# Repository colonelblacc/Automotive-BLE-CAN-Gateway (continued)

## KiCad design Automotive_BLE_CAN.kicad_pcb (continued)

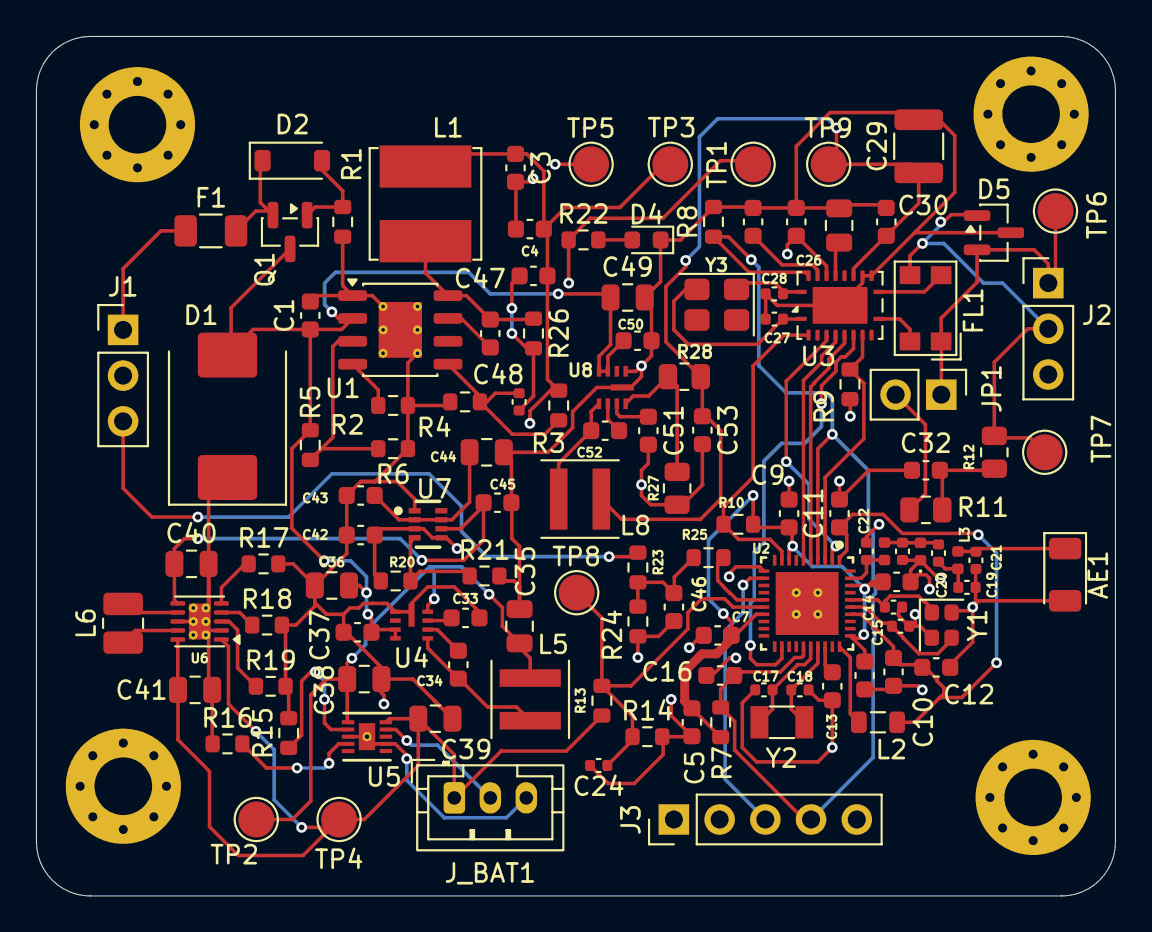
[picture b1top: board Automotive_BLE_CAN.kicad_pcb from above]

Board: 4 copper layers, 59.9 x 47.8 mm, 122 parts (0 on the bottom side), 70 nets.

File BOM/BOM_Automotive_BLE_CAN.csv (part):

Item,Designator,Qty,Value,Description,Package,Manufacturer,MPN,Ratings / Tolerance,Automotive Qual,Alternatives,Notes / Design Intent
1,AE1,1,Antenna_Chip,"2.45 GHz Ceramic Chip Antenna, Peak Gain 1.5 dBi, 50 Ohm",Johanson_2450AT18x100_2400-2500Mhz,Johanson Technology,2450AT18D0100E,,AEC-Q200 qualified option,"Pulse W3008, Taoglas GLA.01",Compact Bluetooth Low Energy omnidirectional antenna
2,C1,1,2.2uF,"2.2uF Ceramic Capacitor, Decoupling",C_0603_1608Metric,Murata / TDK / Taiyo Yuden,GCM188R71E2.2K,"16V / 25V, X7R, ±10%",AEC-Q200 Grade 1,,
3,C2,1,2.2nF,"2.2nF Ceramic Capacitor, Precision / High-Q",C_0603_1608Metric,Murata / TDK / Taiyo Yuden,GCM1885C1H2.2nFA01D,"50V, C0G/NP0 (RF) or X7R, ±5%",AEC-Q200 Grade 1,,
4,"C3, C53",2,22uF,"22uF Ceramic Capacitor, High Capacitance Low ESR",C_0603_1608Metric,Murata / TDK / Taiyo Yuden,GCM21BR71E226KA73L,"25V / 50V, X7R / X7S, ±10%",AEC-Q200 Grade 1,,
5,"C4, C30, C31, C34, C37, C46, C50, C52",8,100nF,"100nF Ceramic Capacitor, Precision / High-Q",C_0603_1608Metric,Murata / TDK / Taiyo Yuden,GCM1885C1H100nFA01D,"50V, C0G/NP0 (RF) or X7R, ±5%",AEC-Q200 Grade 1,,
6,"C5, C6, C7, C8, C9, C10, C11, C16",8,0.1uF,"0.1uF Ceramic Capacitor, Decoupling",C_0603_1608Metric,Murata / TDK / Taiyo Yuden,GCM188R71E0.1K,"16V / 25V, X7R, ±10%",AEC-Q200 Grade 1,,
7,C12,1,10uF,"10uF Ceramic Capacitor, High Capacitance Low ESR",C_0603_1608Metric,Murata / TDK / Taiyo Yuden,GCM21BR71E106KA73L,"25V / 50V, X7R / X7S, ±10%",AEC-Q200 Grade 1,,
8,"C13, C33, C42, C43, C45, C51",6,1uF,"1uF Ceramic Capacitor, Decoupling",C_0603_1608Metric,Murata / TDK / Taiyo Yuden,GCM188R71E1K,"16V / 25V, X7R, ±10%",AEC-Q200 Grade 1,,
9,"C14, C17",2,12pF,"12pF Ceramic Capacitor, Precision / High-Q",C_0402_1005Metric,Murata / TDK / Taiyo Yuden,GCM1555C1H12pFA01D,"50V, C0G/NP0 (RF) or X7R, ±5%",AEC-Q200 Grade 1,,
10,C15,1,10pF,"10pF Ceramic Capacitor, Precision / High-Q",C_0402_1005Metric,Murata / TDK / Taiyo Yuden,GCM1555C1H10pFA01D,"50V, C0G/NP0 (RF) or X7R, ±5%",AEC-Q200 Grade 1,,
11,"C18, C20",2,15pF,"15pF Ceramic Capacitor, Precision / High-Q",C_0402_1005Metric,Murata / TDK / Taiyo Yuden,GCM1555C1H15pFA01D,"50V, C0G/NP0 (RF) or X7R, ±5%",AEC-Q200 Grade 1,,
12,C19,1,1.2pF,"1.2pF Ceramic Capacitor, Precision / High-Q",C_0402_1005Metric,Murata / TDK / Taiyo Yuden,GCM1555C1H1.2pFA01D,"50V, C0G/NP0 (RF) or X7R, ±5%",AEC-Q200 Grade 1,,
13,C21,1,0.7pF,"0.7pF Ceramic Capacitor, Precision / High-Q",C_0402_1005Metric,Murata / TDK / Taiyo Yuden,GCM1555C1H0.7pFA01D,"50V, C0G/NP0 (RF) or X7R, ±5%",AEC-Q200 Grade 1,,
14,"C22, C23",2,1.5pF,"1.5pF Ceramic Capacitor, Precision / High-Q",C_0402_1005Metric,Murata / TDK / Taiyo Yuden,GCM1555C1H1.5pFA01D,"50V, C0G/NP0 (RF) or X7R, ±5%",AEC-Q200 Grade 1,,
15,C24,1,100nF,"100nF Ceramic Capacitor, Precision / High-Q",C_0402_1005Metric,Murata / TDK / Taiyo Yuden,GCM1555C1H100nFA01D,"50V, C0G/NP0 (RF) or X7R, ±5%",AEC-Q200 Grade 1,,
16,C25,1,330nF,"330nF Ceramic Capacitor, Precision / High-Q",C_0603_1608Metric,Murata / TDK / Taiyo Yuden,GCM1885C1H330nFA01D,"50V, C0G/NP0 (RF) or X7R, ±5%",AEC-Q200 Grade 1,,
17,"C27, C28",2,8.2pF,"8.2pF Ceramic Capacitor, Precision / High-Q",C_0402_1005Metric,Murata / TDK / Taiyo Yuden,GCM1555C1H8.2pFA01D,"50V, C0G/NP0 (RF) or X7R, ±5%",AEC-Q200 Grade 1,,
18,C29,1,10uF,"10uF Ceramic Capacitor, High Capacitance Low ESR",C_1210_3225Metric,Murata / TDK / Taiyo Yuden,GCM21BR71E106KA73L,"25V / 50V, X7R / X7S, ±10%",AEC-Q200 Grade 1,,
19,C32,1,4.7nF,"4.7nF Ceramic Capacitor, Precision / High-Q",C_0603_1608Metric,Murata / TDK / Taiyo Yuden,GCM1885C1H4.7nFA01D,"50V, C0G/NP0 (RF) or X7R, ±5%",AEC-Q200 Grade 1,,
20,"C35, C40",2,22uF,"22uF Ceramic Capacitor, High Capacitance Low ESR",C_0805_2012Metric,Murata / TDK / Taiyo Yuden,GCM21BR71E226KA73L,"25V / 50V, X7R / X7S, ±10%",AEC-Q200 Grade 1,,
21,"C36, C49",2,2.2uF,"2.2uF Ceramic Capacitor, Decoupling",C_0805_2012Metric,Murata / TDK / Taiyo Yuden,GCM188R71E2.2K,"16V / 25V, X7R, ±10%",AEC-Q200 Grade 1,,
22,"C38, C39",2,4.7uF,"4.7uF Ceramic Capacitor, Decoupling",C_0805_2012Metric,Murata / TDK / Taiyo Yuden,GCM188R71E4.7K,"16V / 25V, X7R, ±10%",AEC-Q200 Grade 1,,
23,"C26, C41, C44",3,10uF,"10uF Ceramic Capacitor, High Capacitance Low ESR",C_0805_2012Metric,Murata / TDK / Taiyo Yuden,GCM21BR71E106KA73L,"25V / 50V, X7R / X7S, ±10%",AEC-Q200 Grade 1,,
24,C47,1,1.0nF,"1.0nF Ceramic Capacitor, Precision / High-Q",C_0603_1608Metric,Murata / TDK / Taiyo Yuden,GCM1885C1H1.0nFA01D,"50V, C0G/NP0 (RF) or X7R, ±5%",AEC-Q200 Grade 1,,
25,C48,1,100pF,"100pF Ceramic Capacitor, Precision / High-Q",C_0402_1005Metric,Murata / TDK / Taiyo Yuden,GCM1555C1H100pFA01D,"50V, C0G/NP0 (RF) or X7R, ±5%",AEC-Q200 Grade 1,,
26,D1,1,D_TVS,"36V Bidirectional Automotive TVS Diode, 400W Peak Pulse Power",D_SMC,Bourns / Littelfuse,SMAJ36CA,,"AEC-Q101, ISO 7637-2 / ISO 16750-2",TPSMAJ36CA,Primary vehicle input transient & load-dump surge protection
27,D2,1,15V,15V 500mW Zener Diode,D_SOD-123,Diodes Inc,BZT52C15-7-F,,AEC-Q101,MMSZ5245B,P-FET gate clamp protection against over-voltage
28,D3,1,D_TVS,70V 70mA Dual Schottky Barrier Diode,D_0402_1005Metric,Vishay,BAS70-04,,AEC-Q101,BAT54S,Fast clamp steering diode
29,D4,1,LED,70V 70mA Dual Schottky Barrier Diode,LED_0603_1608Metric,Vishay,BAS70-04,,AEC-Q101,BAT54S,Fast clamp steering diode
30,D5,1,D_TVS_Dual_AAC,Automotive Dual Bidirectional Transil ESD Protection for CAN bus,SOT-23,STMicroelectronics,ESDCAN24-2BWY,,"AEC-Q101, ISO 10605 (±30kV air/contact)","NUP2105L, PESD2CAN",Protects TCAN4550 CANH/CANL pins against ESD & automotive spikes
31,F1,1,2A (provisional),"2.0A, 125V Fast-Acting Surface Mount Fuse",Fuse_1206_3216Metric,Littelfuse,0451002.MRL,,AEC-Q200,"0154002.DR, CC12H2A",Vehicle input catastrophic overcurrent fuse
32,FL1,1,Filter_EMI_CommonMode,Automotive Common-Mode Choke 51uH for CAN-Bus / CAN FD,L_CommonModeChoke_Coilcraft_1812CAN,TDK,ACT45B-510-2P-TL003,,AEC-Q200 Grade 1,DLW43SH510XK2L,Filters common-mode RF noise and emissions on CAN bus (CISPR 25)
33,"J1, J2",2,Conn_01x03_Pin,"3-pin 3.5mm Automotive Screw Terminal (VIN, GND, IGN)",PinHeader_1x03_P2.54mm_Vertical,Phoenix Contact / JST / Wurth,Phoenix Contact 1984620 (PT 1.5/3-3.5-H),,Automotive / High Temp UL94V-0,,
34,J3,1,Conn_01x05_Pin,5-pin Micro SWD Debug & Programming Header (1.27mm),PinHeader_1x05_P2.54mm_Vertical,Phoenix Contact / JST / Wurth,Samtec FTSH-105-01-L-DV,,Automotive / High Temp UL94V-0,,
35,J_BAT1,1,Conn_01x03_Pin,2-pin JST-PH 2.0mm Shrouded Battery Connector,JST_PH_B3B-PH-K_1x03_P2.00mm_Vertical,Phoenix Contact / JST / Wurth,JST S2B-PH-K-S,,Automotive / High Temp UL94V-0,,
36,JP1,1,Conn_01x02_Pin,2-pin 2.54mm Header with Jumper Shunt (120 Ohm CAN Termination),PinHeader_1x02_P2.54mm_Vertical,Harwin / Samtec,M20-9990245,,AEC-Q200 / Industrial,,
37,L1,1,47uH,22uH Shielded Power Inductor for LM5164 Buck,L_Bourns_SRN6045TA,Coilcraft / TDK / Würth,"XAL5030-223MEB (22uH, 2.1A)","High Saturation Current, Shielded",AEC-Q200 Grade 1,,
38,L2,1,10uH,10uH Power Inductor / RF Choke,L_0805_2012Metric,Coilcraft / TDK / Würth,LQW15AN10uH,"High Saturation Current, Shielded",AEC-Q200 Grade 1,,
39,L3,1,2nH,2nH Power Inductor / RF Choke,L_0402_1005Metric,Coilcraft / TDK / Würth,LQW15AN2nH,"High Saturation Current, Shielded",AEC-Q200 Grade 1,,
40,L4,1,2.8nH,2.8nH Power Inductor / RF Choke,L_0402_1005Metric,Coilcraft / TDK / Würth,LQW15AN2.8nH,"High Saturation Current, Shielded",AEC-Q200 Grade 1,,
41,L6,1,2.2uH,2.2uH Shielded Power Inductor for TPS63900 Buck-Boost,L_1008_2520Metric,Coilcraft / TDK / Würth,"XFL4020-222MEB (2.2uH, 3.5A)","High Saturation Current, Shielded",AEC-Q200 Grade 1,,
42,"L5, L8",2,6.8uH,4.7uH Shielded Power Inductor for LMR36506 Buck,L_Coilcraft_XxL4020,Coilcraft / TDK / Würth,"LPS4018-472MRB (4.7uH, 1.8A)","High Saturation Current, Shielded",AEC-Q200 Grade 1,,
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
